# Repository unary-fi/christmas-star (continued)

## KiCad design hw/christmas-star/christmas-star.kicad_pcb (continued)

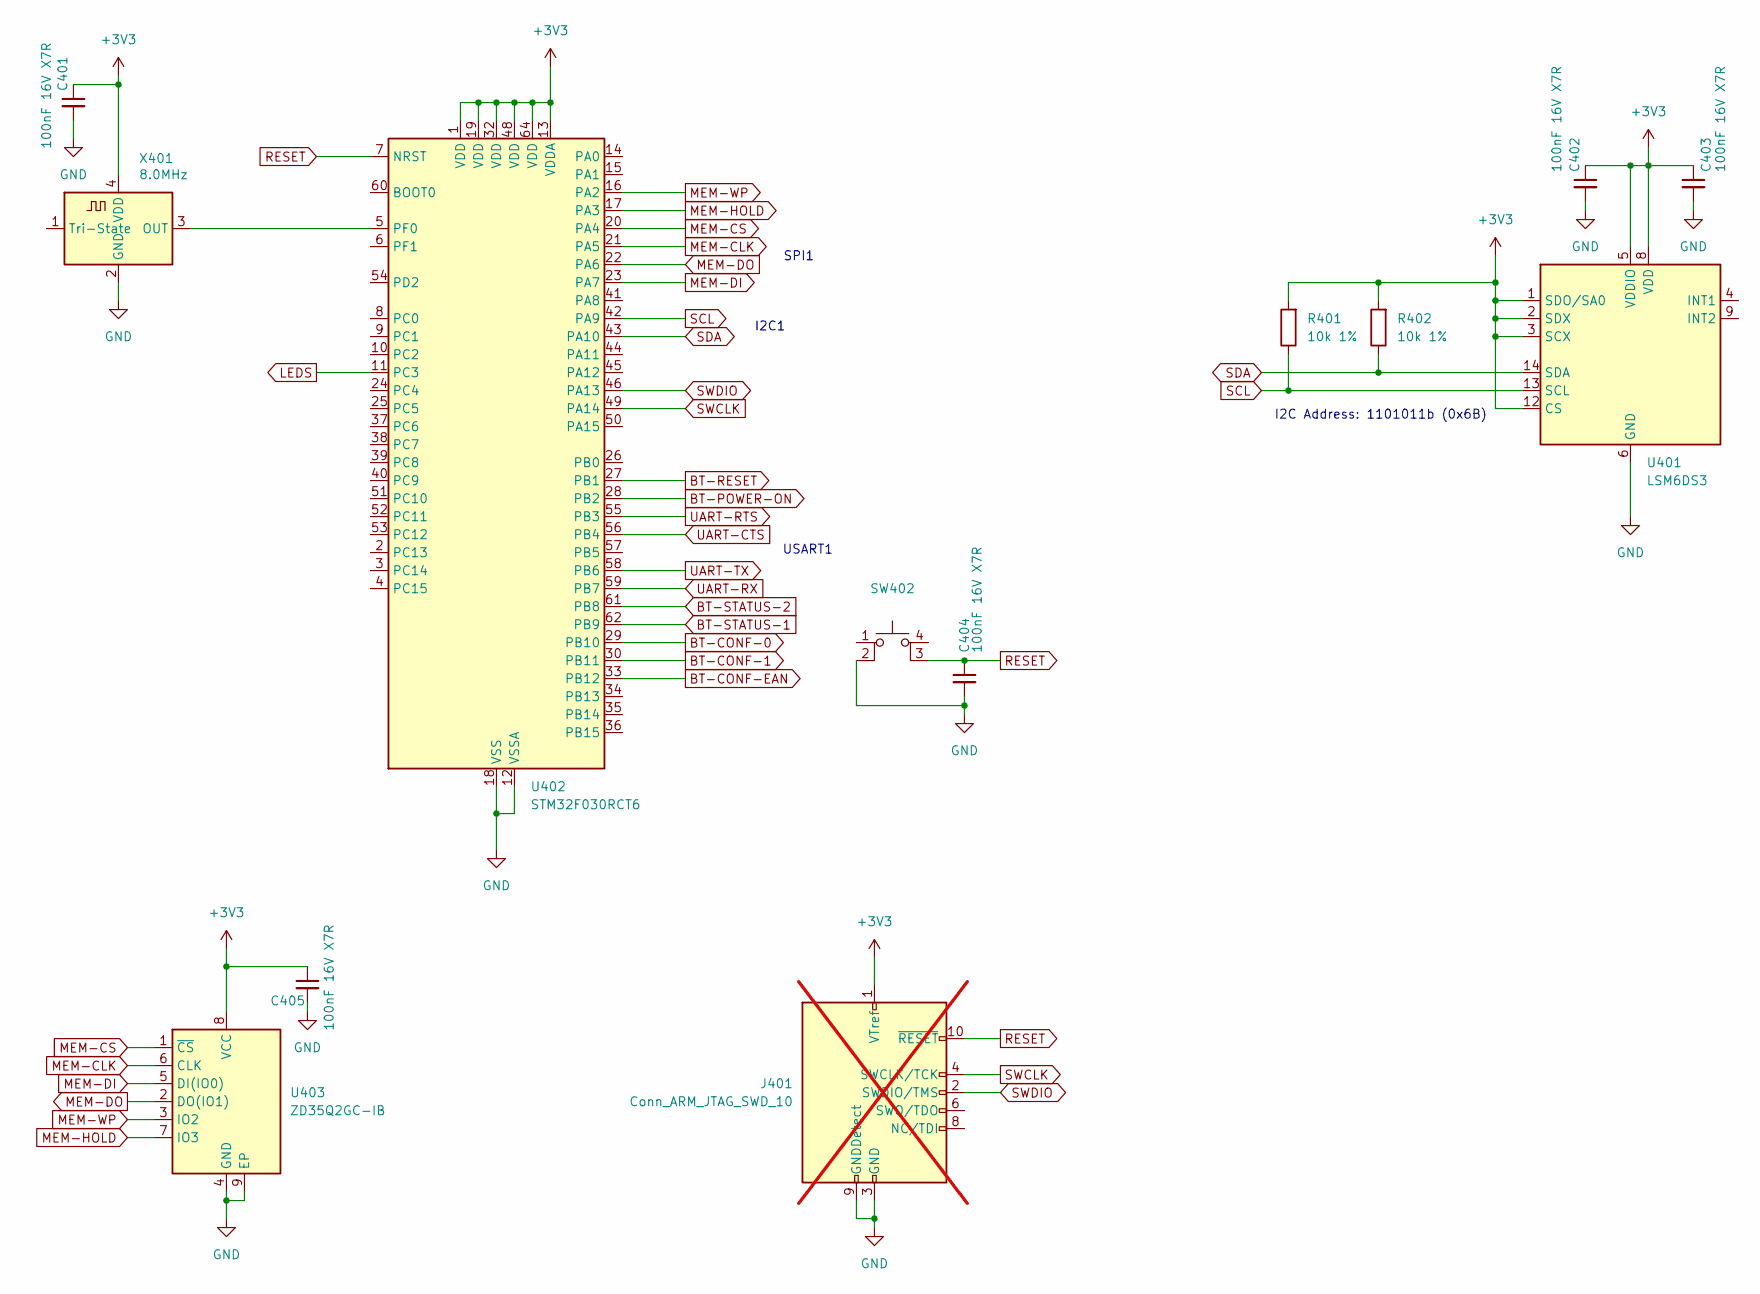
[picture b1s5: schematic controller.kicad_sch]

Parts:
C401, C402, C403, C404, C405: 100nF 16V X7R; C_0402_1005Metric; JLCPCB Part # C328914
J401: Conn_ARM_JTAG_SWD_10; PinHeader_2x05_P1.27mm_Vertical_SMD; JLCPCB Part # C976755; not fitted
R401, R402: 10k 1%; R_0402_1005Metric; JLCPCB Part # C2906861
SW402: SW-SMD_4P-L6.2-W6.2-P4.50-LS8.6; JLCPCB Part # C2909692
U401: LSM6DS3; LGA-14_3x2.5mm_P0.5mm_LayoutBorder3x4y; JLCPCB Part # C95230
U402: STM32F030RCT6; LQFP-64_10x10mm_P0.5mm; JLCPCB Part # C81046
U403: ZD35Q2GC-IB; WSON-8-1EP_8x6mm_P1.27mm_EP3.4x4.3mm; JLCPCB Part # C5366334
X401: 8.0MHz; Crystal_SMD_2016-4Pin_2.0x1.6mm; JLCPCB Part # C5563784

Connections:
+3V3: C401.1, C402.1, C403.1, C405.1, J401.1 (VTref), R401.2, R402.2, U401.1 (SDO/SA0), U401.2 (SDX), U401.3 (SCX), U401.5 (VDDIO), U401.8 (VDD), U401.12 (CS), U402.1 (VDD), U402.13 (VDDA), U402.19 (VDD), U402.32 (VDD), U402.48 (VDD), U402.64 (VDD), U403.8 (VCC), X401.4 (VDD); also elsewhere on the board
BT-CONF-0: U402.29 (PB10); also elsewhere on the board
BT-CONF-1: U402.30 (PB11); also elsewhere on the board
BT-CONF-EAN: U402.33 (PB12); also elsewhere on the board
BT-POWER-ON: U402.28 (PB2); also elsewhere on the board
BT-RESET: U402.27 (PB1); also elsewhere on the board
BT-STATUS-1: U402.62 (PB9); also elsewhere on the board
BT-STATUS-2: U402.61 (PB8); also elsewhere on the board
GND: C401.2, C402.2, C403.2, C404.2, C405.2, J401.3 (GND), J401.5 (GND), J401.9 (GNDDetect), SW402.2, U401.6 (GND), U401.7 (GND), U402.12 (VSSA), U402.18 (VSS), U402.31 (VSS), U402.47 (VSS), U402.63 (VSS), U403.4 (GND), U403.9 (EP), X401.2 (GND); also elsewhere on the board
LEDS: U402.11 (PC3); also elsewhere on the board
MEM-CLK: U402.21 (PA5), U403.6 (CLK)
MEM-CS: U402.20 (PA4), U403.1 (~CS)
MEM-DI: U402.23 (PA7), U403.5 (DI(IO0))
MEM-DO: U402.22 (PA6), U403.2 (DO(IO1))
MEM-HOLD: U402.17 (PA3), U403.7 (IO3)
MEM-WP: U402.16 (PA2), U403.3 (IO2)
unnamed: U402.5 (PF0), X401.3 (OUT)
RESET: C404.1, J401.10 (~RESET), SW402.3 (K), U402.7 (NRST)
SCL: R401.1, U401.13 (SCL), U402.42 (PA9)
SDA: R402.1, U401.14 (SDA), U402.43 (PA10)
SWCLK: J401.4 (SWCLK/TCK), U402.49 (PA14)
SWDIO: J401.2 (SWDIO/TMS), U402.46 (PA13)
UART-CTS: U402.56 (PB4); also elsewhere on the board
UART-RTS: U402.55 (PB3); also elsewhere on the board
UART-RX: U402.59 (PB7); also elsewhere on the board
UART-TX: U402.58 (PB6); also elsewhere on the board

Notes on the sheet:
USART1
I2C Address: 1101011b (0x6B)
I2C1
SPI1

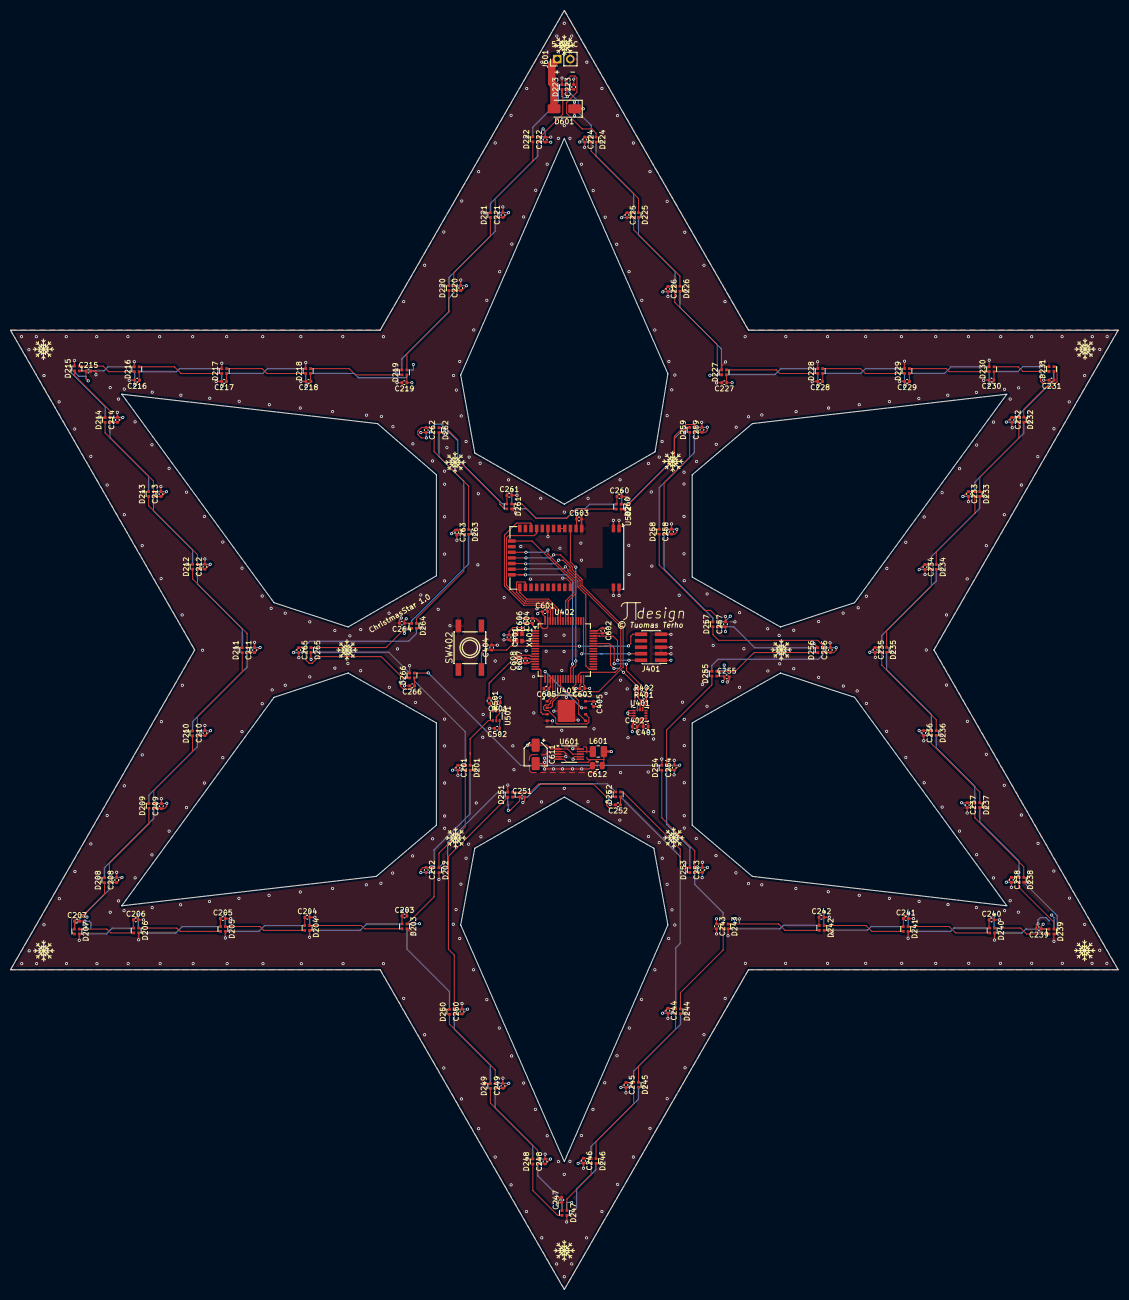
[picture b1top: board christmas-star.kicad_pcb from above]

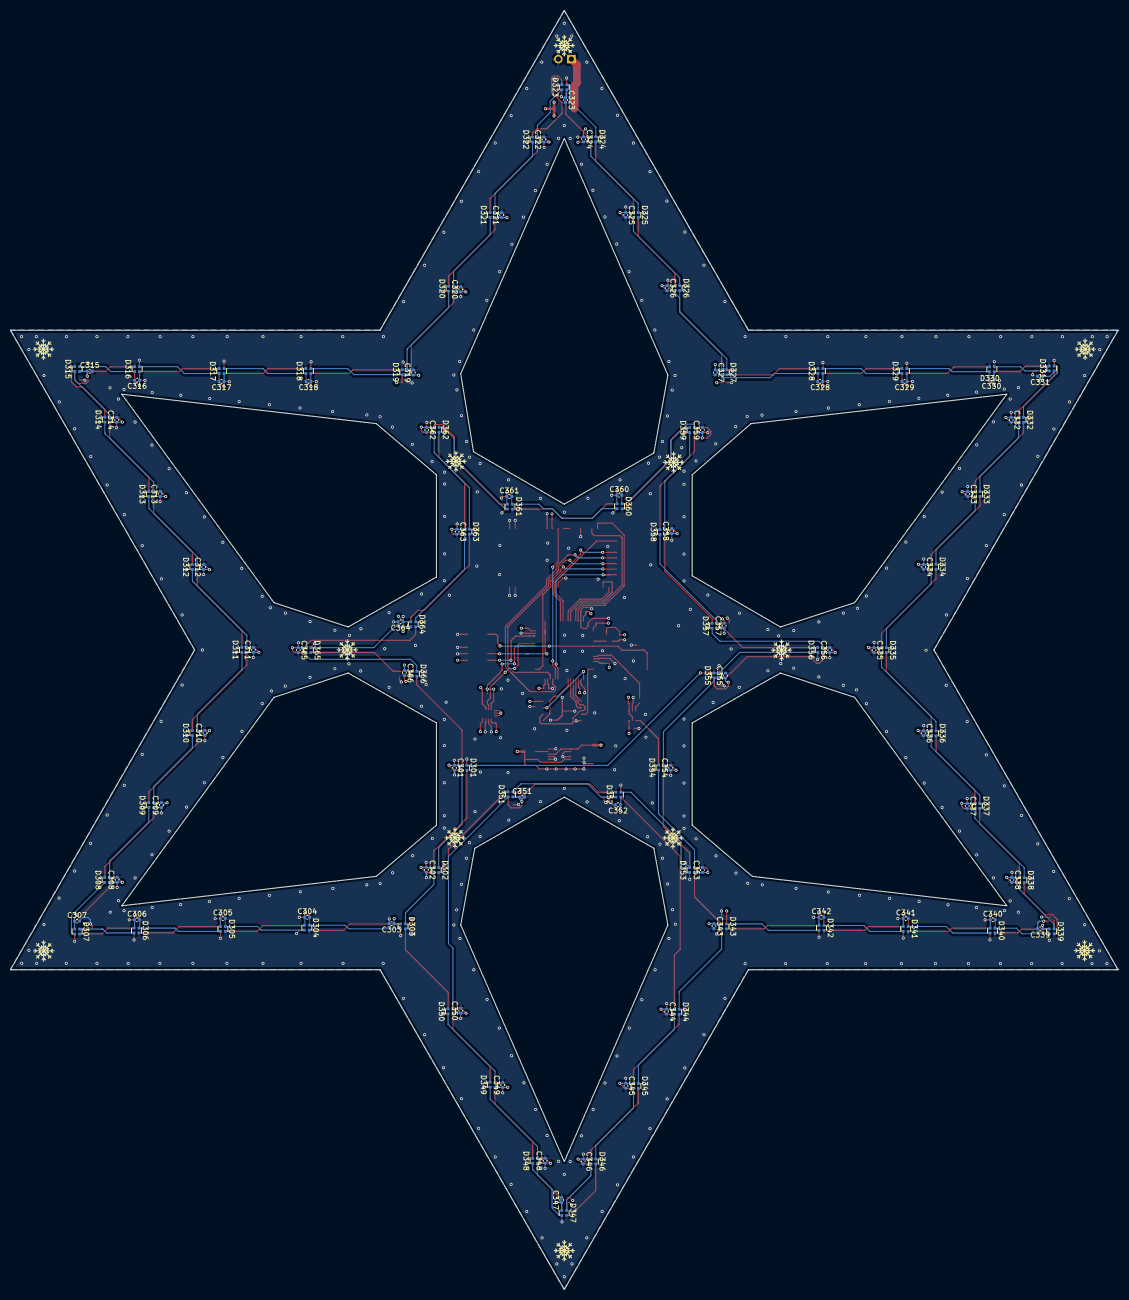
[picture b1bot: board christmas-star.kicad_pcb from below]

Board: 4 copper layers, 216.5 x 250.0 mm, 297 parts (132 on the bottom side), 163 nets.

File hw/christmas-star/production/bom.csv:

Designator,Footprint,Quantity,Value,LCSC Part #
"C201, C202, C203, C204, C205, C206, C207, C208, C209, C210, C211, C212, C213, C214, C215, C216, C217, C218, C219, C220, C221, C222, C223, C224, C225, C226, C227, C228, C229, C230, C231, C232, C233, C234, C235, C236, C237, C238, C239, C240, C241, C242, C243, C244, C245, C246, C247, C248, C249, C250, C251, C252, C253, C254, C255, C256, C257, C258, C259, C260, C261, C262, C263, C264, C265, C266, C301, C302, C303, C304, C305, C306, C307, C308, C309, C310, C311, C312, C313, C314, C315, C316, C317, C318, C319, C320, C321, C322, C323, C324, C325, C326, C327, C328, C329, C330, C331, C332, C333, C334, C335, C336, C337, C338, C339, C340, C341, C342, C343, C344, C345, C346, C347, C348, C349, C350, C351, C352, C353, C354, C355, C356, C357, C358, C359, C360, C361, C362, C363, C364, C365, C366, C401, C402, C403, C404, C405, C501, C502, C601, C602, C603, C604, C605, C607",0402,145,100nF 16V X7R,C328914
"C503, C606",0402,2,10uF 6.3V X5R,C15525
C608,0402,1,1uF 16V X5R,C29266
C611,CP_Elec_4x5.4,1,10uF 25V 15mA,C72484
C612,0805,1,22UF 6.3V X5R,C7467039
"D201, D202, D203, D204, D205, D206, D207, D208, D209, D210, D211, D212, D213, D214, D215, D216, D217, D218, D219, D220, D221, D222, D223, D224, D225, D226, D227, D228, D229, D230, D231, D232, D233, D234, D235, D236, D237, D238, D239, D240, D241, D242, D243, D244, D245, D246, D247, D248, D249, D250, D251, D252, D253, D254, D255, D256, D257, D258, D259, D260, D261, D262, D263, D264, D265, D266, D301, D302, D303, D304, D305, D306, D307, D308, D309, D310, D311, D312, D313, D314, D315, D316, D317, D318, D319, D320, D321, D322, D323, D324, D325, D326, D327, D328, D329, D330, D331, D332, D333, D334, D335, D336, D337, D338, D339, D340, D341, D342, D343, D344, D345, D346, D347, D348, D349, D350, D351, D352, D353, D354, D355, D356, D357, D358, D359, D360, D361, D362, D363, D364, D365, D366",LED_0606,132,DY-S1515065/RGBC/6805-5T,C524053
D601,D_SMA,1,SS38,C64999
"R401, R402",0402,2,10k 1%,C2906861
R501,0402,1,33R 62.5mW,C453643
SW402,SW-SMD_4P-L6.2-W6.2-P4.50-LS8.6,1,~,C2909692
U401,LGA-14_3x2.5mm_P0.5mm_LayoutBorder3x4y,1,LSM6DS3,C95230
U402,LQFP-64_10x10mm_P0.5mm,1,STM32F030RCT6,C81046
U403,WSON-8-1EP_8x6mm_P1.27mm_EP3.4x4.3mm,1,ZD35Q2GC-IB,C5366334
U501,SOT-363_SC-70-6,1,SN74LVC1T45DBV,C9382
U601,VSSOP-10_3x3mm_P0.5mm,1,TPS62056DGS,C182547
X401,Crystal_SMD_2016-4Pin_2.0x1.6mm,1,8.0MHz,C5563784
